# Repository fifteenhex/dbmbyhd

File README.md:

# dbmbyhd
Don't Blame Me if it Burns Your House Down - RT9525GQW LiPo charger breakout

## WHY?!

The RT9525GQW has active power path management that means the load is switched to your
input source instead of the load being powered from the battery while the charger
is trying to charge it. Woot!

## PCBs/Components

- PCB is shared on OSHPark; https://oshpark.com/shared_projects/hrCHnlJL
- The RT9525QGW is available from various suppliers on AliExpress for about $1, On taobao they are about $.50
- Get a cheap 0603 resistor/cap kit for the passives. Buy a stick of 10uF 0805 caps from ebay or whatever.

## Bugs

### Rev 0

- Missing via between gnd fill on the top and bottom layers. Means the iseta resistor and timer cap 
  aren't connected to ground

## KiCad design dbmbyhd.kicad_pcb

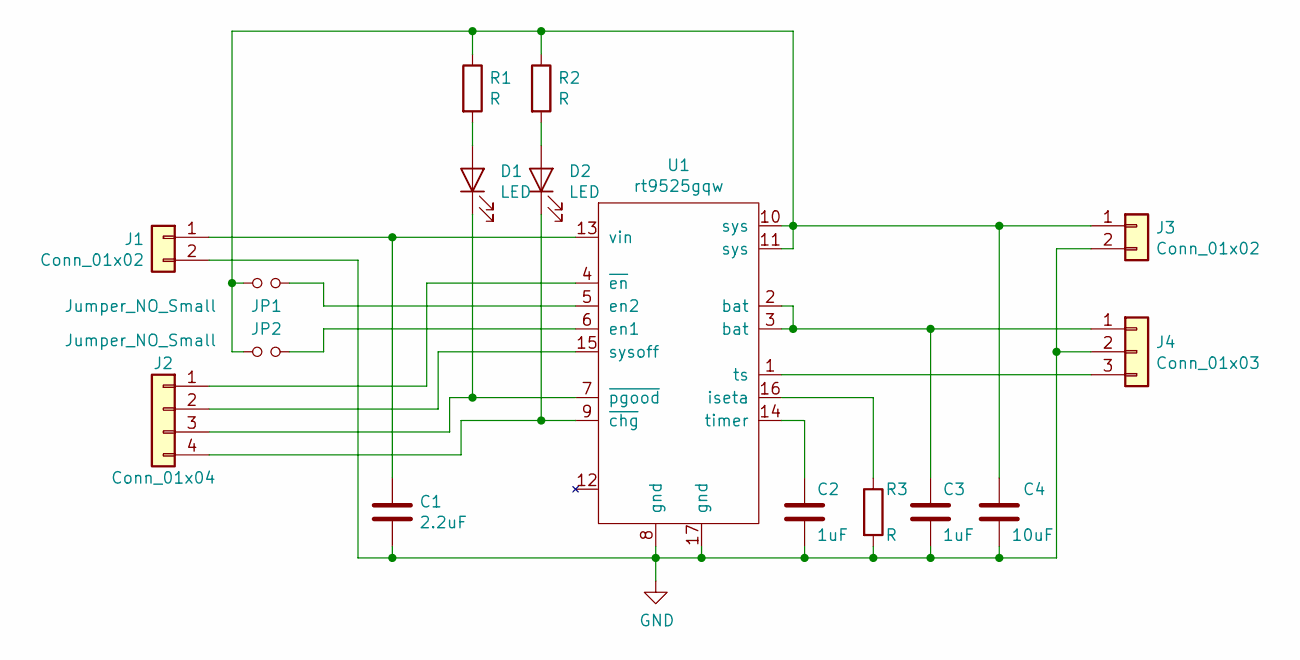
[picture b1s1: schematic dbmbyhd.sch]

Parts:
C1: 2.2uF; C_0603_1608Metric
C2, C3: 1uF; C_0603_1608Metric
C4: 10uF; C_0805_2012Metric
D1, D2: LED; LED_0603_1608Metric
J1, J3: Conn_01x02; PinHeader_1x02_P2.54mm_Vertical
J2: Conn_01x04; PinHeader_1x04_P2.54mm_Vertical
J4: Conn_01x03; PinHeader_1x03_P2.54mm_Vertical
JP1, JP2: Jumper_NO_Small; SolderJumper-2_P1.3mm_Open_TrianglePad1.0x1.5mm
R1, R2, R3: R; R_0603_1608Metric
U1: rt9525gqw; QFN-16-1EP_3x3mm_P0.5mm_EP1.45x1.45mm_ThermalVias

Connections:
GND: C1.2, C2.2, C3.2, C4.2, J1.2, J3.2, J4.2, R3.2, U1.8 (gnd), U1.17 (gnd)
unnamed: C1.1, J1.1, U1.13 (vin)
unnamed: C2.1, U1.14 (timer)
unnamed: C3.1, J4.1, U1.2 (bat), U1.3 (bat)
unnamed: C4.1, J3.1, JP1.1, JP2.1, R1.1, R2.1, U1.10 (sys), U1.11 (sys)
unnamed: D1.1 (K), J2.3, U1.7 (~pgood)
unnamed: D1.2 (A), R1.2
unnamed: D2.1 (K), J2.4, U1.9 (~chg)
unnamed: D2.2 (A), R2.2
unnamed: J2.1, U1.4 (~en)
unnamed: J2.2, U1.15 (sysoff)
unnamed: J4.3, U1.1 (ts)
unnamed: JP1.2, U1.5 (en2)
unnamed: JP2.2, U1.6 (en1)
unnamed: R3.1, U1.16 (iseta)

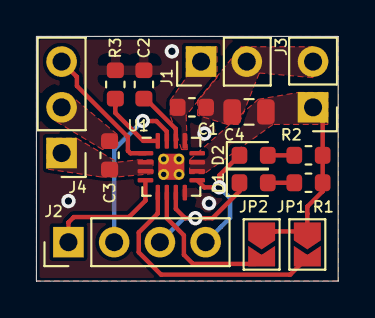
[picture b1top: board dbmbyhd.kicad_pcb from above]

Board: 2 copper layers, 16.8 x 13.6 mm, 16 parts (0 on the bottom side), 15 nets.

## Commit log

2020-03-07 Add project Add symbol for rt9525
2020-03-08 Rev0
2020-03-26 Add some pretty photos
2020-04-04 rev1
